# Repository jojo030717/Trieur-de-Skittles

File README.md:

Bienvenue sur la page de mon projet Trieur de Skittles. Vous trouverez ici tous les fichiers sources nécessaires pour reproduire ce projet.

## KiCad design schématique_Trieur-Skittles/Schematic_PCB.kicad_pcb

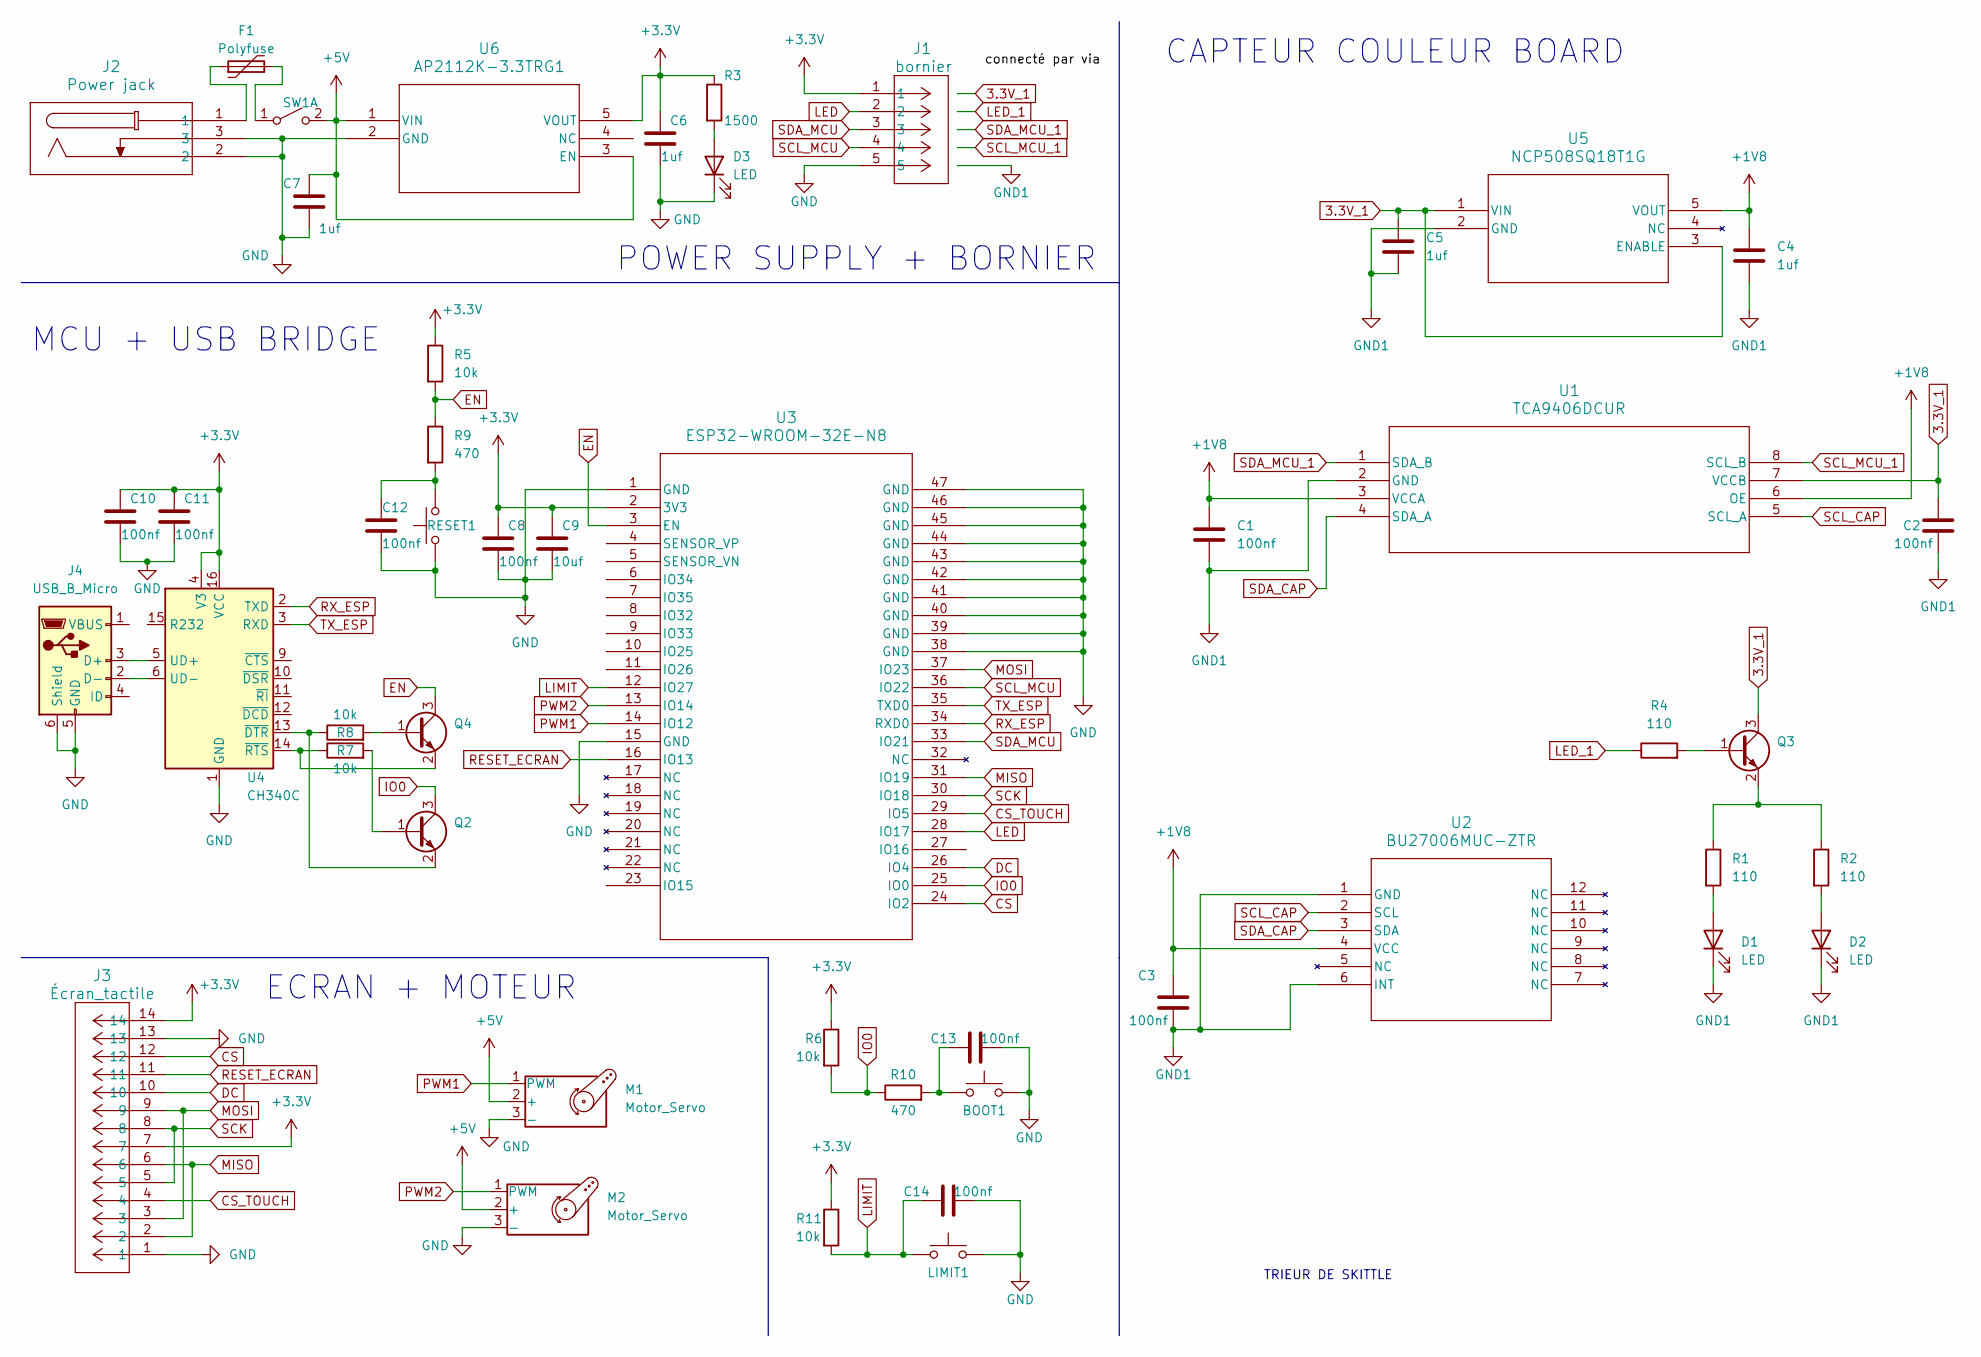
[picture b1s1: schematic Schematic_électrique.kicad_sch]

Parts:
BOOT1: SW_B3F-6000_OMR
C1, C2, C3, C8, C10, C11, C12, C13, C14: 100nf; C_0805_2012Metric_Pad1.18x1.45mm_HandSolder
C4, C5, C6, C7: 1uf; C_0805_2012Metric_Pad1.18x1.45mm_HandSolder
C9: 10uf; C_Radial_D6.3mm_H5.0mm_P2.50mm
D1, D2: LED; LED_D5.0mm
D3: LED; LED_APT3216LSECK_J3-PRV
F1: Polyfuse; 0ZCH_BEL
J1: bornier; OSTVN05A150
J2: Power jack; CUI_PJ-002B
J3: Écran_tactile; CON_702461404_MOL
J4: USB_B_Micro; USB_Micro_amazon_type
LIMIT1: PinHeader_1x02_P2.54mm_Vertical
M1, M2: Motor_Servo; PinHeader_1x03_P2.54mm_Vertical
Q2, Q3, Q4: 2N3055; SOT-23_1_DIO
R1, R2, R4: 110; R_0805_2012Metric_Pad1.20x1.40mm_HandSolder
R3: 1500; R_0805_2012Metric_Pad1.20x1.40mm_HandSolder
R5, R6, R7, R8, R11: 10k; R_0805_2012Metric_Pad1.20x1.40mm_HandSolder
R9, R10: 470; R_0805_2012Metric_Pad1.20x1.40mm_HandSolder
RESET1: SW_B3F-6000_OMR
SW1: PinHeader_1x02_P2.54mm_Vertical
U1: TCA9406DCUR; DCU8
U2: BU27006MUC-ZTR; WQFN12_WQFN12X2520A_ROM-M
U3: ESP32-WROOM-32E-N8; ESP32­WROOM­32E_EXP
U4: CH340C; SOIC-16_3.9x9.9mm_P1.27mm
U5: NCP508SQ18T1G; SC-88A_ONS-M
U6: AP2112K-3.3TRG1; SOT_RG1_DIO-M

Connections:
3.3V_1: C2.2, C5.2, Q3.3 (C), U1.7 (VCCB), U5.1 (VIN), U5.3 (ENABLE)
+1V8: C1.1, C3.1, C4.2, U1.3 (VCCA), U1.6 (OE), U2.4 (VCC), U5.5 (VOUT)
+3.3V: C6.2, C8.2, C9.2, C10.2, C11.2, J1.1, J3.7, J3.14, R3.1, R5.1, R6.1, R11.1, U3.2 (3V3), U4.4 (V3), U4.16 (VCC), U6.5 (VOUT)
+5V: C7.1, M1.2 (+), M2.2 (+), SW1.2 (B), U6.1 (VIN), U6.3 (EN)
CS: J3.12, U3.24 (IO2)
CS_TOUCH: J3.4, U3.29 (IO5)
DC: J3.10, U3.26 (IO4)
EN: Q4.3 (C), R5.2, R9.1, U3.3 (EN)
GND: BOOT1.2, C6.1, C7.2, C8.1, C9.1, C10.1, C11.1, C12.1, C13.1, C14.1, D3.1 (K), J1.5, J2.2, J2.3, J3.1, J3.13, J4.5 (GND), J4.6 (Shield), LIMIT1.2, M1.3 (-), M2.3 (-), RESET1.1, U3.1 (GND), U3.15 (GND), U3.38 (GND), U3.39 (GND), U3.40 (GND), U3.41 (GND), U3.42 (GND), U3.43 (GND), U3.44 (GND), U3.45 (GND), U3.46 (GND), U3.47 (GND), U4.1 (GND), U6.2 (GND)
GND1: C1.2, C2.1, C3.2, C4.1, C5.1, D1.1 (K), D2.1 (K), U1.2 (GND), U2.1 (GND), U2.6 (INT), U5.2 (GND)
IO0: Q2.3 (C), R6.2, R10.1, U3.25 (IO0)
LED: J1.2, U3.28 (IO17)
LED_1: R4.1
LIMIT: C14.2, LIMIT1.1, R11.2, U3.12 (IO27)
MISO: J3.2, J3.6, U3.31 (IO19)
MOSI: J3.3, J3.9, U3.37 (IO23)
unnamed: BOOT1.1, C13.2, R10.2
unnamed: C12.2, R9.2, RESET1.2
unnamed: D1.2 (A), R1.2
unnamed: D2.2 (A), R2.2
unnamed: D3.2 (A), R3.2
unnamed: F1.1, J2.1
unnamed: J4.3 (D+), U4.5 (UD+)
unnamed: J4.2 (D-), U4.6 (UD-)
unnamed: Q2.1 (B), R7.2
unnamed: Q2.2 (E), R8.1, U4.13 (~DTR)
unnamed: Q3.1 (B), R4.2
unnamed: Q3.2 (E), R1.1, R2.1
unnamed: Q4.1 (B), R8.2
unnamed: Q4.2 (E), R7.1, U4.14 (~RTS)
unnamed: F1.2, SW1.1 (A)
PWM1: M1.1 (PWM), U3.14 (IO12)
PWM2: M2.1 (PWM), U3.13 (IO14)
RESET_ECRAN: J3.11, U3.16 (IO13)
RX_ESP: U3.34 (RXD0), U4.2 (TXD)
SCK: J3.5, J3.8, U3.30 (IO18)
SCL_CAP: U1.5 (SCL_A), U2.2 (SCL)
SCL_MCU: J1.4, U3.36 (IO22)
SCL_MCU_1: U1.8 (SCL_B)
SDA_CAP: U1.4 (SDA_A), U2.3 (SDA)
SDA_MCU: J1.3, U3.33 (IO21)
SDA_MCU_1: U1.1 (SDA_B)
TX_ESP: U3.35 (TXD0), U4.3 (RXD)

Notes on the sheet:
MCU + USB BRIDGE
CAPTEUR COULEUR BOARD
TRIEUR DE SKITTLE
POWER SUPPLY + BORNIER
ECRAN + MOTEUR

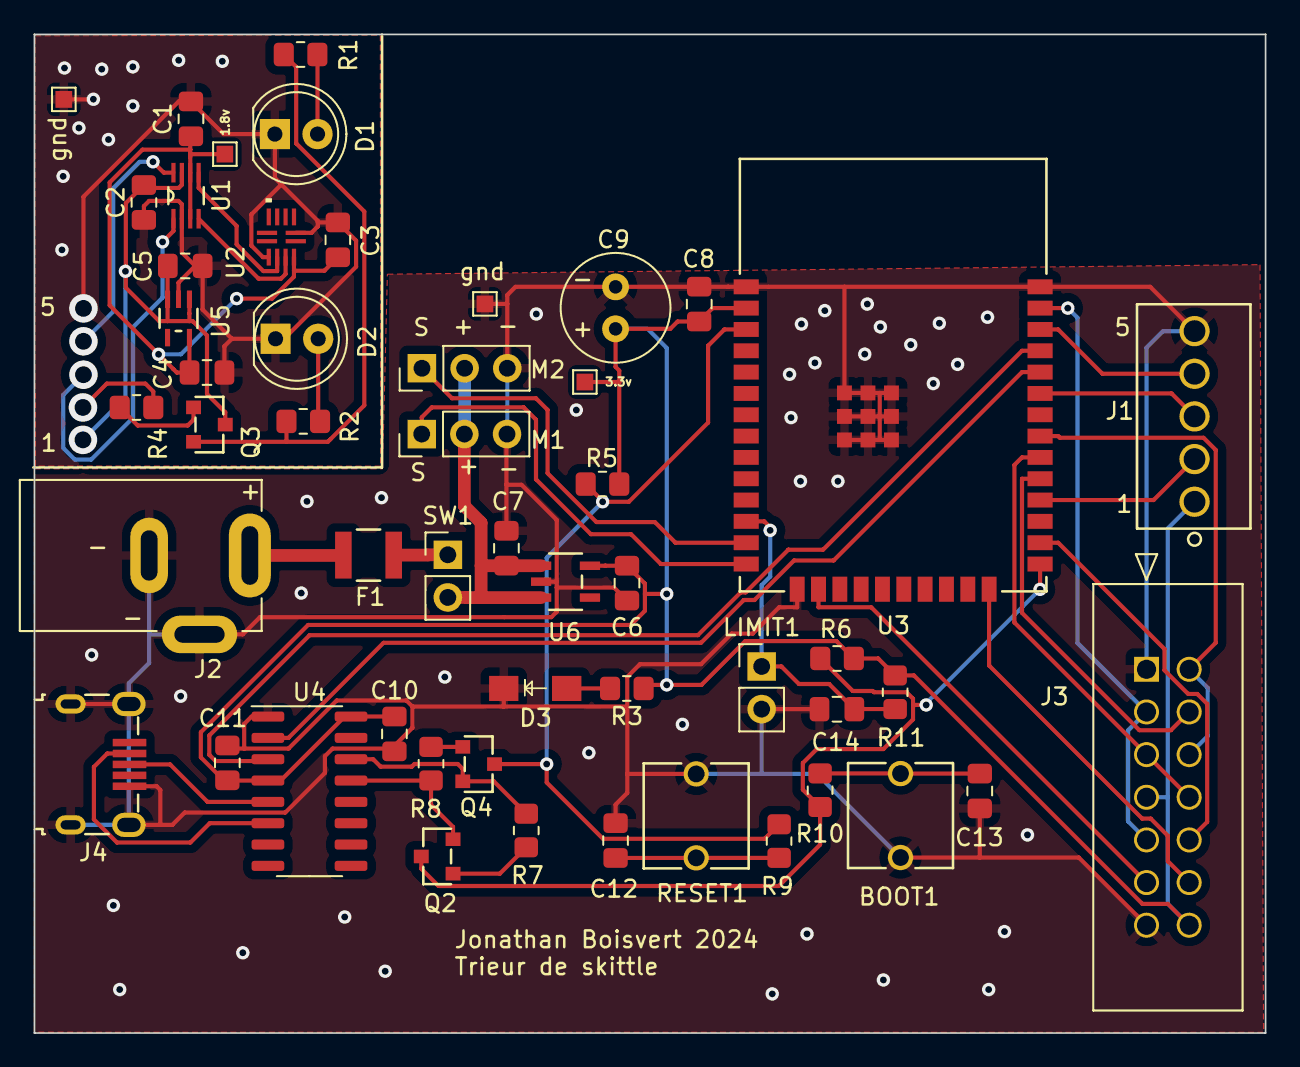
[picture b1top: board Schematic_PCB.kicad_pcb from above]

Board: 2 copper layers, 73.3 x 59.5 mm, 48 parts (0 on the bottom side), 40 nets.

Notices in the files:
parts and their libraries:
Copyright 2016 Accelerated Designs. All rights reserved.
